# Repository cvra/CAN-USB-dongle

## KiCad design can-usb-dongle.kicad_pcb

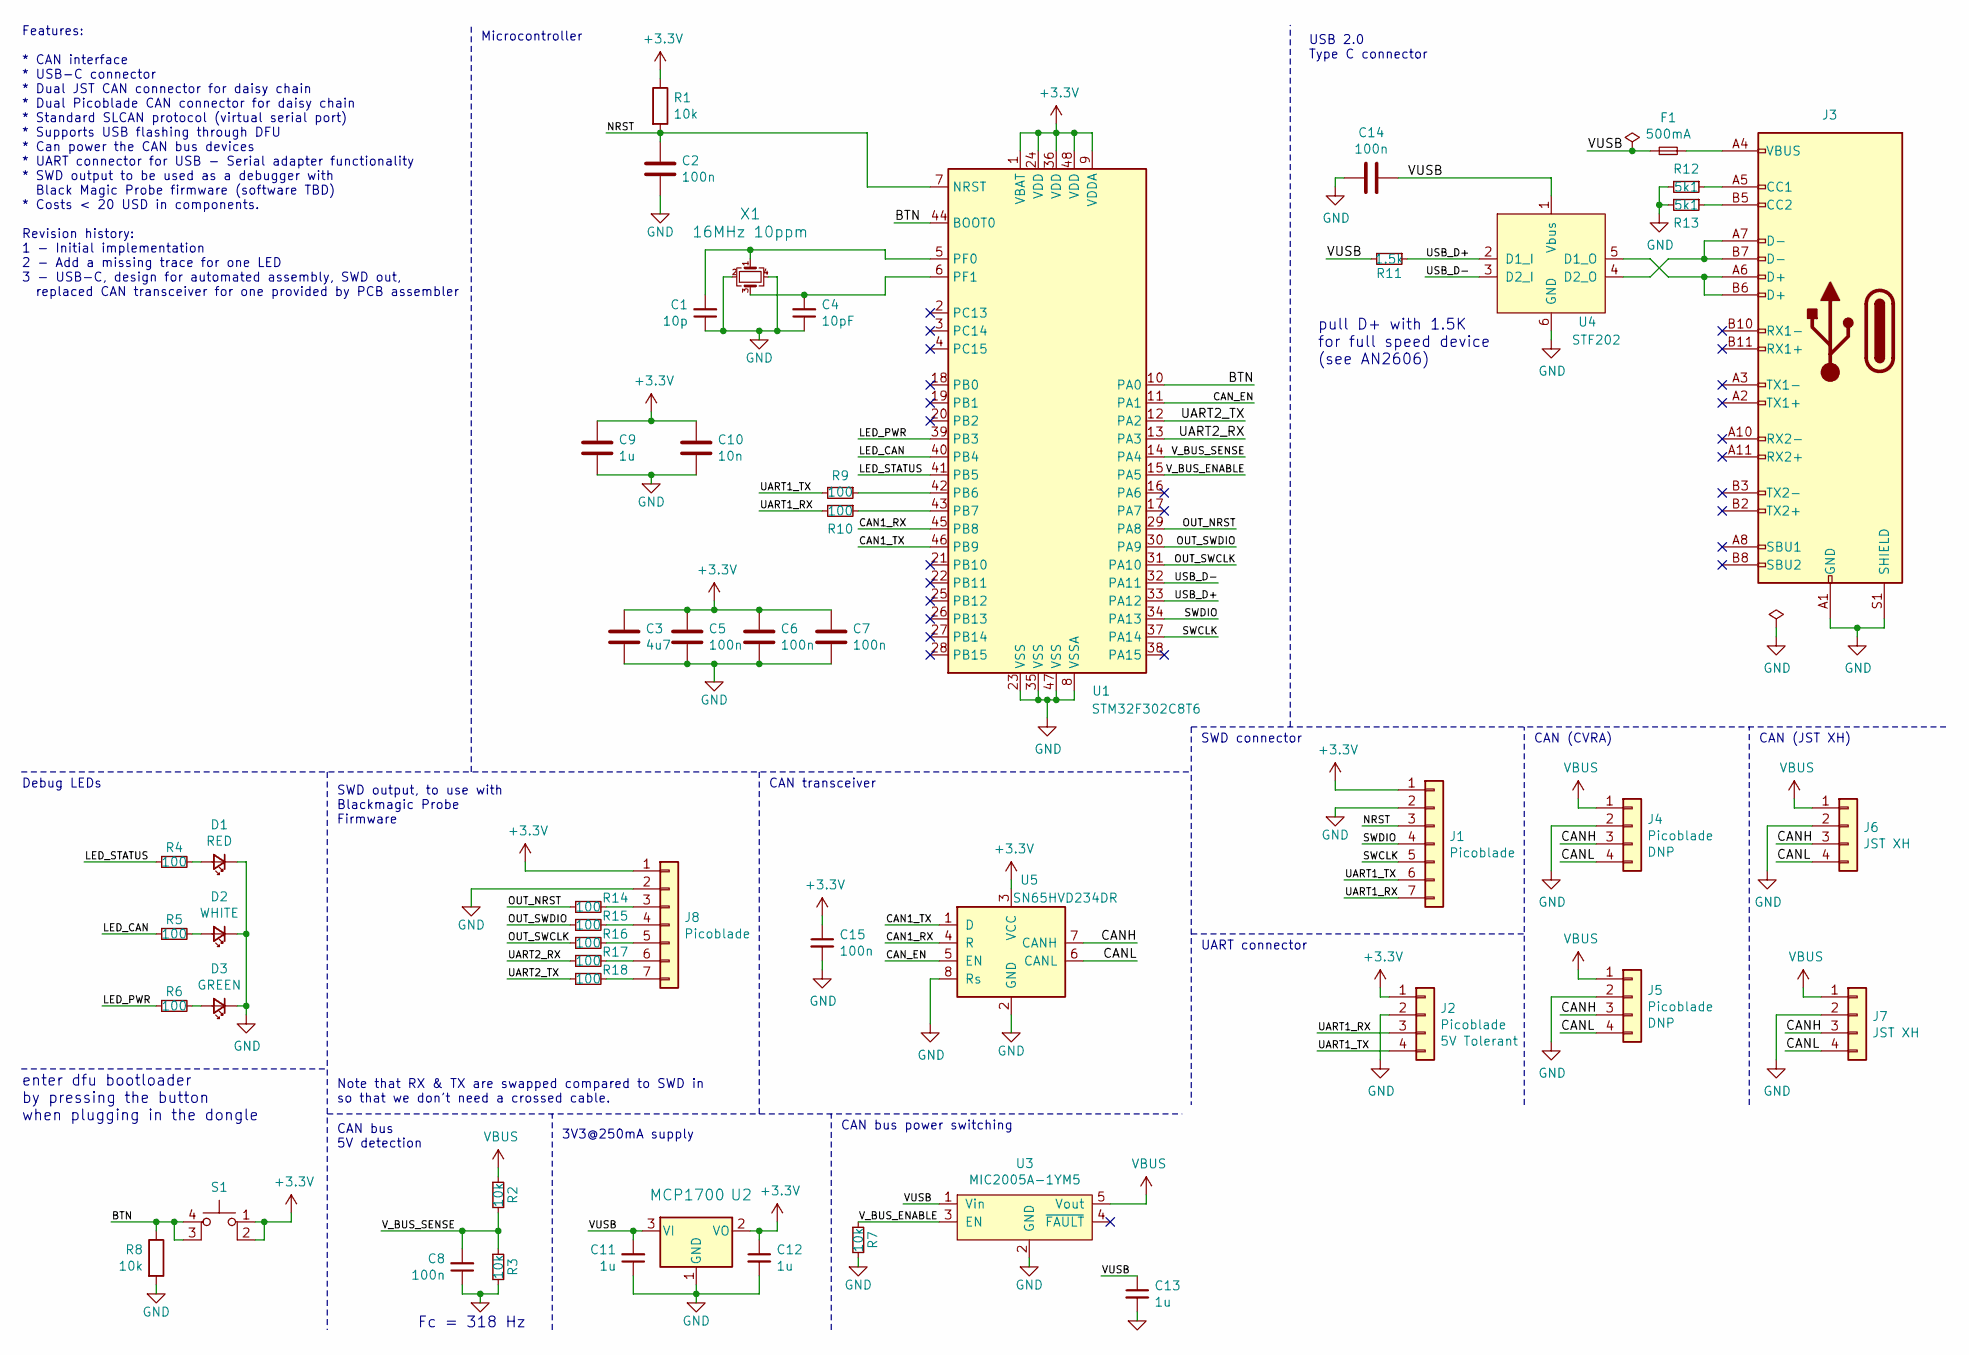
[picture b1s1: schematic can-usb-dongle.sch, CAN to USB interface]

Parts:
C1: 10p; C_0402_1005Metric; lcsc C1546
C2, C5, C6, C7, C8, C14, C15: 100n; C_0402_1005Metric; lcsc C1525
C3: 4u7; C_0402_1005Metric; lcsc C23733
C4: 10pF; C_0402_1005Metric; lcsc C1546
C9, C11, C12, C13: 1u; C_0402_1005Metric; lcsc C52923
C10: 10n; C_0402_1005Metric; lcsc C15195
D1: RED; C_0603_1608Metric; lcsc C72044
D2: WHITE; C_0603_1608Metric; lcsc C83955
D3: GREEN; C_0603_1608Metric; lcsc C72042
F1: 500mA; R_0805; lcsc C261942
J1, J8: Picoblade; Molex_PicoBlade_53261-0771_1x07-1MP_P1.25mm_Horizontal
J2: Picoblade; Molex_PicoBlade_53261-0471_1x04-1MP_P1.25mm_Horizontal; Tolerance 5V Tolerant
J3: XUNPU TYPEC-304S-ACP16; TYPEC-304S-ACP16; lcsc C720630
J4, J5: Picoblade; Molex_PicoBlade_53261-0471_1x04-1MP_P1.25mm_Horizontal
J6, J7: JST XH; JST_XH_S4B-XH-A-1_1x04_P2.50mm_Horizontal
R1, R2, R3, R7, R8: 10k; R_0402_1005Metric; lcsc C25744
R4, R5, R6, R9, R10, R14, R15, R16, R17, R18: 100; R_0402_1005Metric; lcsc C25076
R11: 1.5k; R_0402_1005Metric; lcsc C25867
R12, R13: 5k1; R_0402_1005Metric; lcsc C25905
S1: SW_MEC_5E; TS-1187A-B-A-B; lcsc C318884
U1: STM32F302C8T6; LQFP-48_7x7mm_P0.5mm; lcsc C90795
U2: MCP1700; SOT-23; LCSC C39051
U3: MIC2005A-1YM5; SOT-23-5; lcsc C81399
U4: STF202; TSOP-6_1.65x3.05mm_P0.95mm; lcsc C233431
U5: SN65HVD234DR; SOIC-8_3.9x4.9mm_P1.27mm; LCSC C99818
X1: 16MHz 10ppm; Crystal_SMD_TXC_7M-4Pin_3.2x2.5mm; LCSC C13738

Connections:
+3V3: C3.1, C5.1, C6.1, C7.1, C9.1, C10.1, C12.1, C15.1, J1.1, J2.1, J8.1, R1.1, S1.1, S1.2, U1.1 (VBAT), U1.9 (VDDA), U1.24 (VDD), U1.36 (VDD), U1.48 (VDD), U2.2 (VO), U5.3 (VCC)
/BTN: R8.1, S1.3 (K), S1.4 (A), U1.10 (PA0), U1.44 (BOOT0)
/CAN1_RX: U1.45 (PB8), U5.4 (R)
/CAN1_TX: U1.46 (PB9), U5.1 (D)
/CANH: J4.3, J5.3, J6.3, J7.3, U5.7 (CANH)
/CANL: J4.4, J5.4, J6.4, J7.4, U5.6 (CANL)
/CAN_EN: U1.11 (PA1), U5.5 (EN)
/LED_CAN: R5.1, U1.40 (PB4)
/LED_PWR: R6.1, U1.39 (PB3)
/LED_STATUS: R4.1, U1.41 (PB5)
/NRST: C2.1, J1.3, R1.2, U1.7 (NRST)
/OUT_NRST: R14.1, U1.29 (PA8)
/OUT_SWCLK: R16.1, U1.31 (PA10)
/OUT_SWDIO: R15.1, U1.30 (PA9)
/SWCLK: J1.5, U1.37 (PA14)
/SWDIO: J1.4, U1.34 (PA13)
/UART1_RX: J1.7, J2.3, R9.2
/UART1_TX: J1.6, J2.4, R10.2
/UART2_RX: R17.1, U1.13 (PA3)
/UART2_TX: R18.1, U1.12 (PA2)
/USB_D+: R11.1, U1.33 (PA12), U4.2 (D1_I)
/USB_D-: U1.32 (PA11), U4.3 (D2_I)
/VUSB: C11.2, C13.1, C14.1, F1.1, R11.2, U2.3 (VI), U3.1 (Vin), U4.1 (Vbus)
/V_BUS_ENABLE: R7.1, U1.15 (PA5), U3.3 (EN)
/V_BUS_SENSE: C8.2, R2.2, R3.1, U1.14 (PA4)
GND: C1.1, C2.2, C3.2, C4.1, C5.2, C6.2, C7.2, C8.1, C9.2, C10.2, C11.1, C12.2, C13.2, C14.2, C15.2, D1.1 (K), D2.1 (K), D3.1 (K), J1.2, J2.2, J3.A1 (GND), J3.A12 (GND), J3.B1 (GND), J3.B12 (GND), J3.S1 (SHIELD), J4.2, J5.2, J6.2, J7.2, J8.2, R3.2, R7.2, R8.2, R12.2, R13.2, U1.8 (VSSA), U1.23 (VSS), U1.35 (VSS), U1.47 (VSS), U2.1 (GND), U3.2 (GND), U4.6 (GND), U5.2 (GND), U5.8 (Rs), X1.2, X1.4
unnamed: C1.2, U1.5 (PF0), X1.1
unnamed: C4.2, U1.6 (PF1), X1.3
unnamed: D1.2 (A), R4.2
unnamed: D2.2 (A), R5.2
unnamed: D3.2 (A), R6.2
unnamed: F1.2, J3.A4 (VBUS), J3.A9 (VBUS), J3.B4 (VBUS), J3.B9 (VBUS)
unnamed: J3.A5 (CC1), R12.1
unnamed: J3.A6 (D+), J3.B6 (D+), U4.5 (D1_O)
unnamed: J3.A7 (D-), J3.B7 (D-), U4.4 (D2_O)
unnamed: J3.B5 (CC2), R13.1
unnamed: J8.3, R14.2
unnamed: J8.4, R15.2
unnamed: J8.5, R16.2
unnamed: J8.6, R17.2
unnamed: J8.7, R18.2
unnamed: R9.1, U1.43 (PB7)
unnamed: R10.1, U1.42 (PB6)
VBUS: J4.1, J5.1, J6.1, J7.1, R2.1, U3.5 (Vout)

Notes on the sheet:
enter dfu bootloader by pressing the button when plugging in the dongle
pull D+ with 1.5K for full speed device (see AN2606)
Fc = 318 Hz
Features: * CAN interface * USB-C connector * Dual JST CAN connector for daisy chain * Dual Picoblade CAN connector for daisy chain * Standard SLCAN protocol (virtual serial port) * Supports USB flashing through DFU * Can power the CAN bus devices * UART connector for USB - Serial adapter functiona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
CAN (CVRA)
CAN (JST XH)
3V3@250mA supply
CAN bus 5V detection
SWD connector
UART connector
CAN transceiver
USB 2.0 Type C connector
SWD output, to use with Blackmagic Probe Firmware
Microcontroller
Debug LEDs
CAN bus power switching
Note that RX & TX are swapped compared to SWD in so that we don't need a crossed cable.

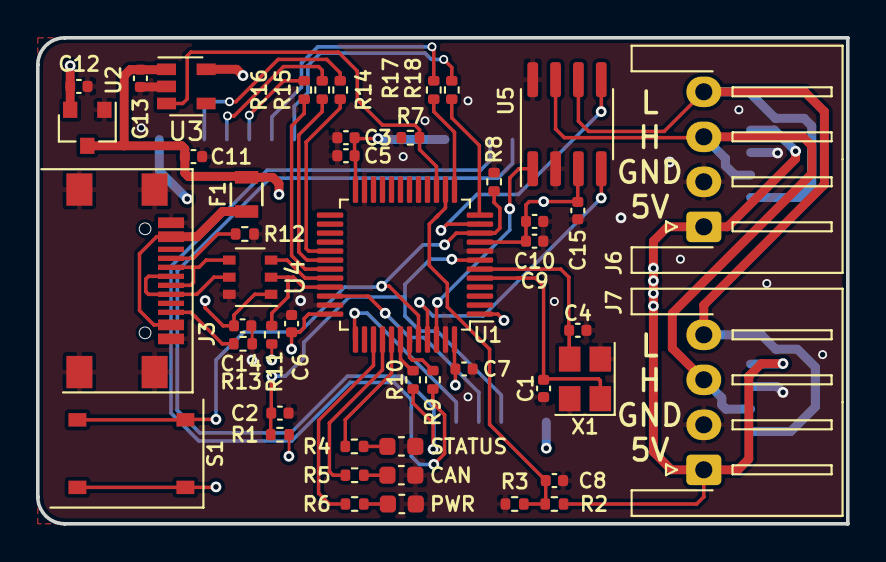
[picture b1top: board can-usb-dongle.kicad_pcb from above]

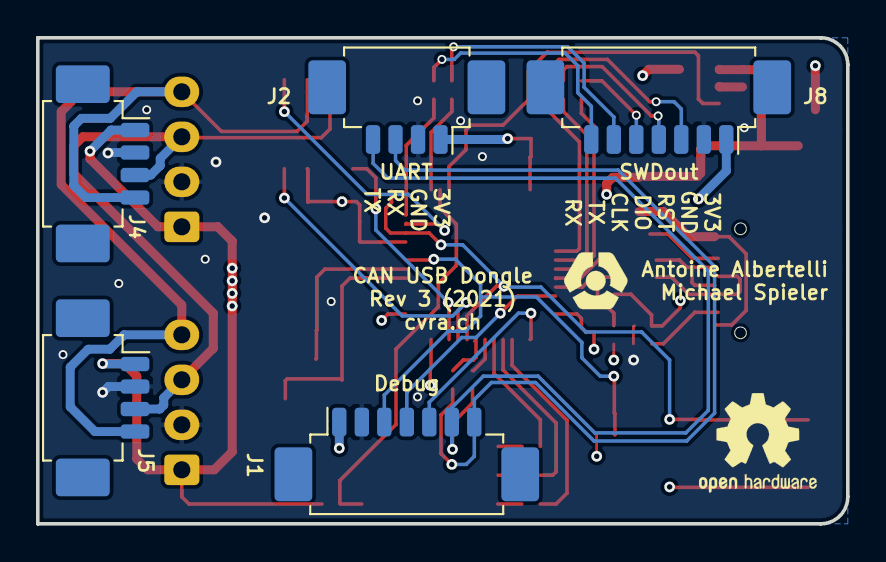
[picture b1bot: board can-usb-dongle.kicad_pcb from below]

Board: 4 copper layers, 45.0 x 27.0 mm, 52 parts (5 on the bottom side), 44 nets.

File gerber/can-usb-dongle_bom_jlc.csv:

"Comment","Designator","Footprint","LCSC Part #"
"10p","C1","C_0402_1005Metric","C1546"
"4u7","C3","C_0402_1005Metric","C23733"
"10pF","C4","C_0402_1005Metric","C1546"
"100n","C8,C5,C6,C7,C2,C14,C15","C_0402_1005Metric","C1525"
"10n","C10","C_0402_1005Metric","C15195"
"1u","C11,C12,C13,C9","C_0402_1005Metric","C52923"
"RED","D1","C_0603_1608Metric","C72044"
"WHITE","D2","C_0603_1608Metric","C83955"
"GREEN","D3","C_0603_1608Metric","C72042"
"500mA","F1","R_0805","C261942"
"XUNPU TYPEC-304S-ACP16","J3","TYPEC-304S-ACP16","C720630"
"10k","R7,R2,R3,R8,R1","R_0402_1005Metric","C25744"
"100","R9,R10,R6,R4,R5,R14,R15,R16,R17,R18","R_0402_1005Metric","C25076"
"1.5k","R11","R_0402_1005Metric","C25867"
"5k1","R13,R12","R_0402_1005Metric","C25905"
"SW_MEC_5E","S1","TS-1187A-B-A-B","C318884"
"STM32F302C8T6","U1","LQFP-48_7x7mm_P0.5mm","C90795"
"MCP1700","U2","SOT-23","C39051"
"MIC2005A-1YM5","U3","SOT-23-5","C81399"
"STF202","U4","TSOP-6_1.65x3.05mm_P0.95mm","C233431"
"SN65HVD234DR","U5","SOIC-8_3.9x4.9mm_P1.27mm","C99818"
"16MHz 10ppm","X1","Crystal_SMD_TXC_7M-4Pin_3.2x2.5mm","C13738"

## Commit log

2015-05-24 Add kicad library submodule
2015-05-24 Start with schematic.
2015-05-24 note differnt possible CAN transceivers.
2015-06-30 Switch to STM32F3 LQFP48 with only 1 CAN interface.
2015-08-19 Changes to reduce cost.
2015-09-09 start assigning footprints.
2015-09-09 Add datasheets.
2015-09-30 Add V_BUS sense and LED, USB pull resistors.
2015-09-30 Remove PWR LED.
2015-09-30 Remove duplicate 1.5k USB D+ pullup.
2015-10-02 USB protection, more capacitors.
    - Add NUF2042 ESD proctection for USB
    - Correct fuse placement
    - Add capacitors to CAN transceiver and SiP32431 switch.
2015-10-02 Rearrange symbols.
2015-10-19 Start with footrpint placement on PCB
2015-10-19 Add more datasheets
2015-10-20 Most components placed.
2015-10-20 Connect CAN bus power LED to GPIO, update connector footprints.
2015-10-20 Change DRC minimal dimmensions
2015-10-20 PCB layer setting, correct edge cut layer
2015-10-21 Change pinout to optimize routing.
2015-10-21 All components roughly placed.
2015-10-21 Start routing
2015-10-22 Most traces fixed, need for optimization.
2015-10-22 optimize traces
2015-10-22 Better LED placement, change VCC routing
2015-10-22 Optimize VCC routing, redo power supply.
2015-10-22 Add GND fill zone, DRC check corrections
2015-10-23 Improve GND connection with vias
2015-10-23 Update kicad lib with missing footprints
2015-10-23 Add CVRA logo, silk screen text
2015-10-23 Change USB footprint back to slot version
2015-10-24 GND connection, tracks
2015-10-24 Start with bill of materials
2015-10-24 Modify silkscreen text
2015-10-24 Update footprints (USB, voltage regulator)
2015-10-24 Remove datasheets of unused components
2015-10-24 Resolve GPIO conflict with JTAG pin
    V_BUS_ENABLE and CAN_SILENT were in conflict with JTAG output pins.
    They had to be moved because at boot time the output value cannot be guaranteed.
2015-10-24 Fix floating via
2015-10-24 Resolve JTAG pin conflict, add V_BUS_SENSE filter cap
2015-10-24 Fix silkscreen text
2015-10-24 Increase component dinstance on backside for handsoldering
2015-10-25 Select DigiKey components
2015-10-25 Add CVRA logo to schematic
2015-10-25 Add solder mask clearance, fix missing F.Paste at USB pads
2015-10-25 add 5% solder paste clearance
2015-10-25 Update schematic date
2015-10-25 Add fabrication files
2015-10-25 Add pdf schematic
2015-11-09 Update kicad-lib
2015-11-09 Latest BOM version
2015-11-09 Add PCB images.
2015-11-09 Add README
2015-11-18 Remove redundant doc.
2015-11-22 Update LED resistor values.
2015-11-22 Start RevB, add missing STATUS LED track
2015-11-23 Colored schematic PDF.
2016-02-27 Add missing datasheets
2021-02-14 Rough layout of gen3
2021-02-17 Remove old datasheets, add new ones
2021-02-19 Change power switch for one in stock
2021-03-01 Finalize routing, ready for review
2021-03-07 Address comments by nuft@
    * Document the change of CAN transceiver
    * Swap RX/TX on SWD output
    * Add silkscreen describing led function
    * fix silkscreen text size
2021-03-09 Put the SWDout UART on UART2
2021-03-09 fix silkscreen
2021-03-14 Add gerber files for gen3
2023-01-08 Add schematics of old CAN USB dongles

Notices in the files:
can-usb-dongle.sch:
Creative Commons CC0
